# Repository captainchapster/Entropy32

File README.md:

# Entropy32

**Entropy32** (aka *The Universe Bifurcator*) is a dedicated Bitcoin seed phrase generator that uses radioactive decay as its entropy source. It's completely open source and designed to be simple, auditable, and buildable by anyone with readily available components.

## Why radioactive decay?

Pseudo-random number generators are deterministic — given the same seed, they always produce the same output. True randomness for something as consequential as a Bitcoin wallet's seed phrase should come from a physical process nobody can predict or manipulate. Radioactive decay is quantum-mechanically random: the timing of individual decay events is fundamentally unpredictable, making it an ideal entropy source for generating cryptographic secrets.

## How it works

1. A Geiger counter detects decay events from a radioactive source (or background) and outputs a pulse via a 3.5mm audio jack.

2. An LM393 comparator IC then takes the 0-1.5V pulse and compares it to a bias of ~0.5V via a voltage divider such that if V>0.5V we get HIGH else LOW.

3. The timing between events is captured and compared in non-overlapping pairs (each inter-arrival time feeds exactly one comparison, so adjacent output bits never share an input interval). Each resulting bit passes two continuous NIST SP 800-90B health tests (Repetition Count Test and Adaptive Proportion Test) before it's fed through SHA-256 conditioning to whiten the raw entropy and remove any bias — if either test trips, the device halts rather than generating a seed from a degraded source.
4. The conditioned entropy is mapped to words from the standard BIP39 English wordlist.
5. A simple button-driven, state-machine UI walks you through generating and displaying your seed phrase — entirely offline, with no wireless connectivity, no persistent storage of the seed, and no software dependencies beyond the device itself.

## Hardware

- Custom PCB built around an [ATmega328P microcontroller](https://ww1.microchip.com/downloads/en/DeviceDoc/Atmel-7810-Automotive-Microcontrollers-ATmega328P_Datasheet.pdf), designed in [KiCad](https://www.kicad.org/)
- Geiger counter module as the entropy source (currently designed to take the 3.5mm output of the [GQ Electronics GMC-320S](https://www.gqelectronicsllc.com/comersus/store/comersus_viewItem.asp?idProduct=5787))
- [LM393 comparator IC](https://www.ti.com/product/LM393)
- Push-button interface for on-device operation
- Serveral common passives i.e. resistors, capacitors, and LEDs
- 7805 voltage regulator 
- 16MHZ crystal oscillator
- 16x2 LCD display with I2C adaptor
- PJ320E 3.5mm audio jack
- DC barrel jack
- header pins

## Repository contents

| File | Purpose |
|---|---|
| `entropy32.ino` | Main firmware — state machine, entropy capture, and UI logic |
| `sha256.h` / `sha256.cpp` | SHA-256 implementation used to condition raw entropy |
| `bip39_wordlist.h` | BIP39 English wordlist, compiled into firmware |
| `button.h` | Button input handling |
| `english.txt` | Source BIP39 wordlist |
| `generate_wordlist.py` | Script to regenerate `bip39_wordlist.h` from `english.txt` |

## Building it yourself

The Arduino sketch (`entropy32.ino`) and its accompanying `.h`/`.cpp` files must remain in the same top-level folder for the Arduino IDE to compile correctly — it doesn't recurse into subfolders for sketch code. Open `entropy32.ino` in the Arduino IDE, verify your board settings for the ATmega328P, and flash as normal.

## Validation

Entropy quality is being validated against the [NIST SP 800-90B](https://csrc.nist.gov/publications/detail/sp/800-90b/final) methodology for entropy sources used in random bit generation.

## Acknowledgements

- **Cosmographer / BHRIGU** — [bhrigu.io](https://www.bhrigu.io) — identified that the original entropy logic compared each inter-arrival time to the one before it (an overlapping comparison), which correlates adjacent output bits even when the underlying intervals are IID. The firmware now uses non-overlapping interval pairs instead. Thank you for the detailed writeup.

## Disclaimer

This is a hobbyist/educational project. If you use it to generate a real Bitcoin seed phrase, understand the risks: verify the entropy quality yourself, review the code, and never trust a seed-generating device (this one included) with significant funds without independent auditing.

## Licenses

- For firmware/software, see [`MIT LICENSE`](./LICENSE).
- For hardware, see [`CERN-OHL-S v2 LICENSE`](./LICENSE-HARDWARE).

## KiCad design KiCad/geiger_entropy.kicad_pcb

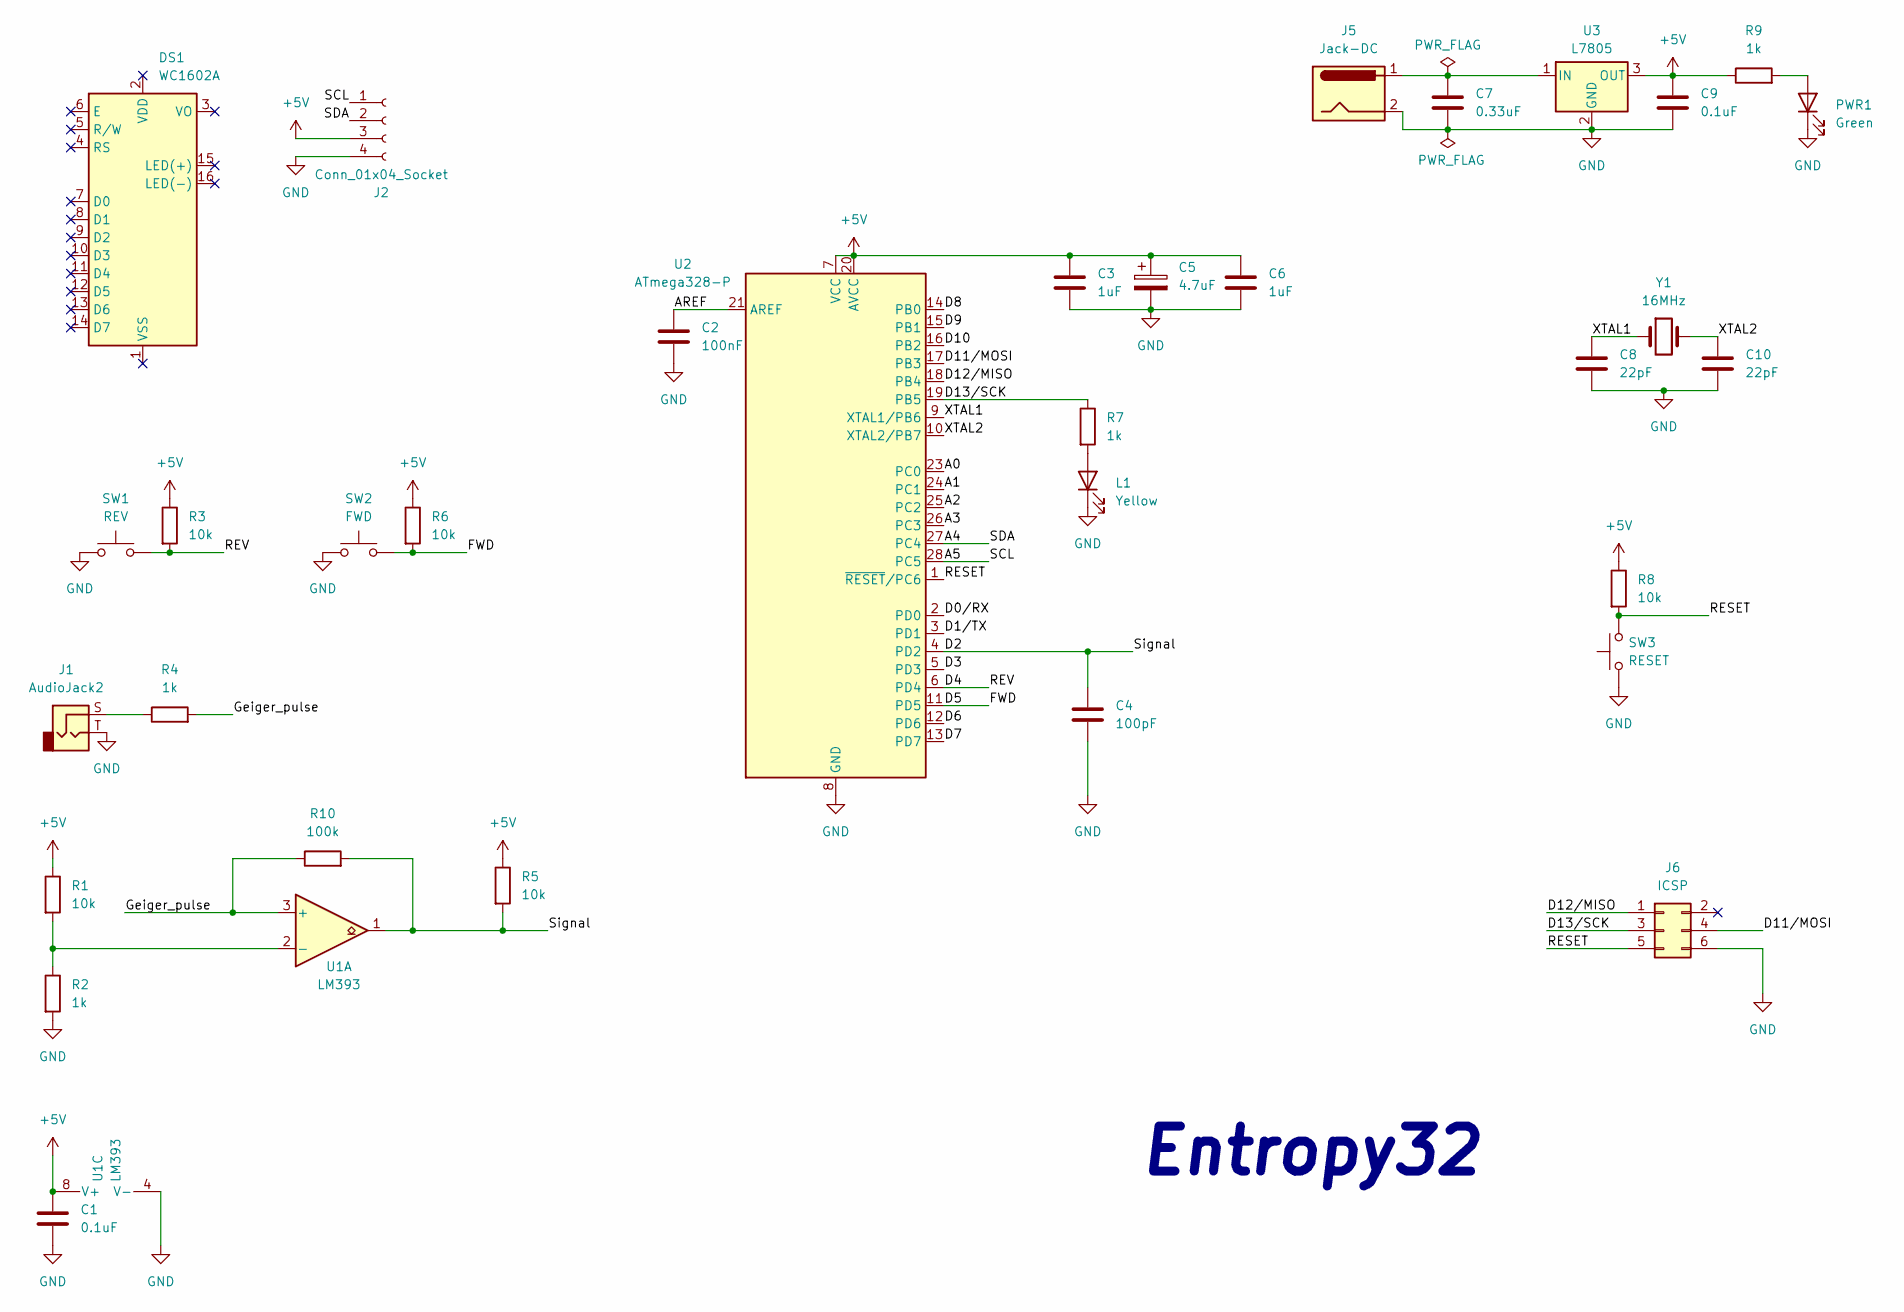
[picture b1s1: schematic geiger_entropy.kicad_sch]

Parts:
C1, C9: 0.1uF; C_Disc_D5.0mm_W2.5mm_P5.00mm
C2: 100nF; C_Disc_D5.0mm_W2.5mm_P5.00mm
C3, C6: 1uF; C_Disc_D5.0mm_W2.5mm_P5.00mm
C4: 100pF; C_Disc_D5.0mm_W2.5mm_P5.00mm
C5: 4.7uF; CP_Radial_D5.0mm_P2.00mm
C7: 0.33uF; C_Disc_D5.0mm_W2.5mm_P5.00mm
C8, C10: 22pF; C_Disc_D5.0mm_W2.5mm_P5.00mm
DS1: WC1602A
J1: AudioJack2; Jack_3.5mm_PJ320E_Horizontal
J2: Conn_01x04_Socket; PinHeader_1x04_P2.54mm_Vertical
J5: Jack-DC; BarrelJack_Horizontal
J6: ICSP; PinHeader_2x03_P2.54mm_Vertical
L1: Yellow; LED_D3.0mm
PWR1: Green; LED_D3.0mm
R1, R3, R5, R6, R8: 10k; R_Axial_DIN0207_L6.3mm_D2.5mm_P10.16mm_Horizontal
R2, R4, R7, R9: 1k; R_Axial_DIN0207_L6.3mm_D2.5mm_P10.16mm_Horizontal
R10: 100k; R_Axial_DIN0207_L6.3mm_D2.5mm_P10.16mm_Horizontal
SW1: REV; SW_PUSH_6mm
SW2: FWD; SW_PUSH_6mm
SW3: RESET; SW_PUSH_6mm
U1: LM393; DIP-8_W7.62mm
U2: ATmega328-P; DIP-28_W7.62mm
U3: L7805; TO-220-3_Vertical
Y1: 16MHz; Crystal_HC49-4H_Vertical

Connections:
+5V: C1.1, C3.1, C5.1, C6.1, C9.1, J2.3, R1.1, R3.1, R5.1, R6.1, R8.1, R9.1, U1.8 (V+), U2.7 (VCC), U2.20 (AVCC), U3.3 (OUT)
/A0: U2.23 (PC0)
/A1: U2.24 (PC1)
/A2: U2.25 (PC2)
/A3: U2.26 (PC3)
/A4: J2.2, U2.27 (PC4)
/A5: J2.1, U2.28 (PC5)
/AREF: C2.1, U2.21 (AREF)
/D0/RX: U2.2 (PD0)
/D1/TX: U2.3 (PD1)
/D2: C4.1, R5.2, R10.2, U1.1, U2.4 (PD2)
/D3: U2.5 (PD3)
/D4: R3.2, SW1.2, U2.6 (PD4)
/D5: R6.2, SW2.2, U2.11 (PD5)
/D6: U2.12 (PD6)
/D7: U2.13 (PD7)
/D8: U2.14 (PB0)
/D9: U2.15 (PB1)
/D10: U2.16 (PB2)
/D11/MOSI: J6.4, U2.17 (PB3)
/D12/MISO: J6.1, U2.18 (PB4)
/D13/SCK: J6.3, R7.1, U2.19 (PB5)
/Geiger_pulse: R4.2, R10.1, U1.3 (+)
/RESET: J6.5, R8.2, SW3.2, U2.1 (~RESET/PC6)
/XTAL1: C8.1, U2.9 (XTAL1/PB6), Y1.1
/XTAL2: C10.1, U2.10 (XTAL2/PB7), Y1.2
GND: C1.2, C2.2, C3.2, C4.2, C5.2, C6.2, C7.2, C8.2, C9.2, C10.2, J1.T, J2.4, J5.2, J6.6, L1.1 (K), PWR1.1 (K), R2.2, SW1.1, SW2.1, SW3.1, U1.4 (V-), U2.8 (GND), U2.22 (GND), U3.2 (GND)
unnamed: J1.S, R4.1
unnamed: L1.2 (A), R7.2
unnamed: PWR1.2 (A), R9.2
unnamed: R1.2, R2.1, U1.2 (-)
unnamed: C7.1, J5.1, U3.1 (IN)

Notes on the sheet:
Entropy32

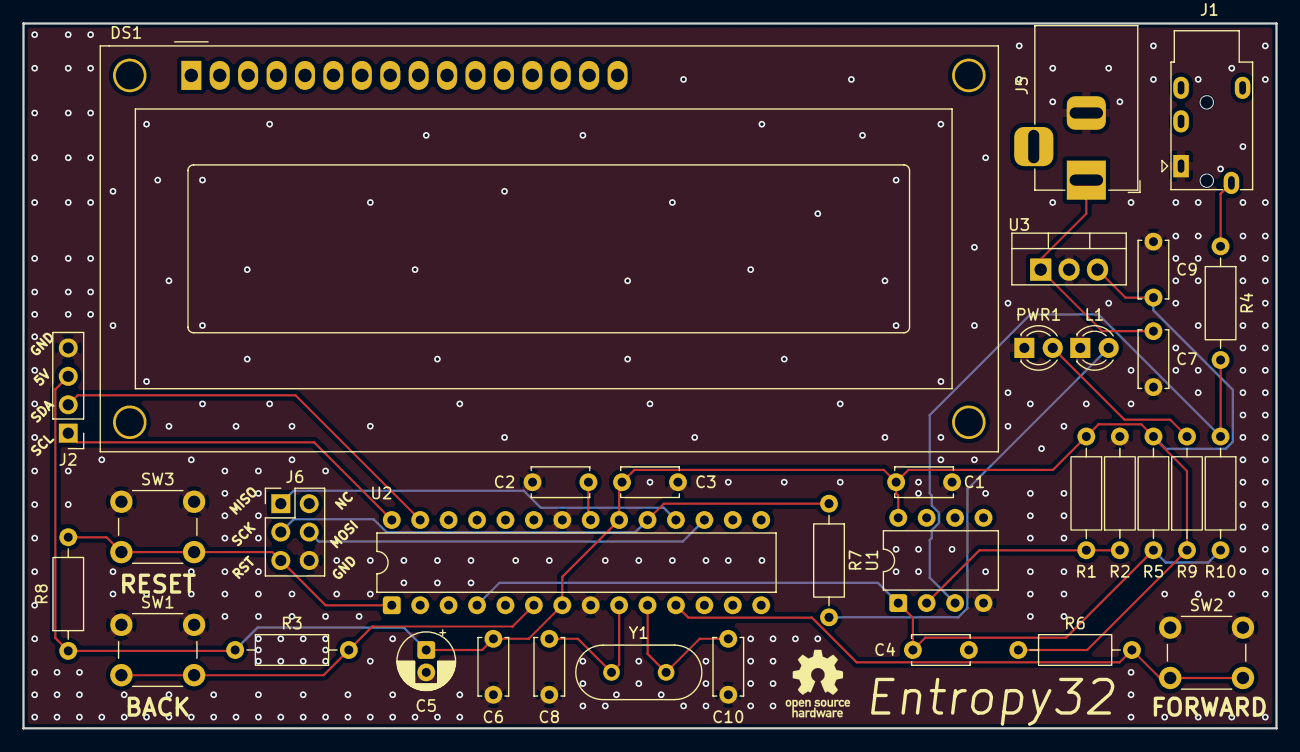
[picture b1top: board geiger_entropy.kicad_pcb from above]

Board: 2 copper layers, 112.0 x 63.0 mm, 34 parts (0 on the bottom side), 20 nets.

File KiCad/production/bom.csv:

Designator,Footprint,Quantity,Value,LCSC Part #
"C1, C9",C_Disc_D5.0mm_W2.5mm_P5.00mm,2,0.1uF,
"C10, C8",C_Disc_D5.0mm_W2.5mm_P5.00mm,2,22pF,
C2,C_Disc_D5.0mm_W2.5mm_P5.00mm,1,100nF,
"C3, C6",C_Disc_D5.0mm_W2.5mm_P5.00mm,2,1uF,
C4,C_Disc_D5.0mm_W2.5mm_P5.00mm,1,100pF,
C5,CP_Radial_D5.0mm_P2.00mm,1,4.7uF,
C7,C_Disc_D5.0mm_W2.5mm_P5.00mm,1,0.33uF,
DS1,WC1602A,1,WC1602A,
J1,Jack_3.5mm_PJ320E_Horizontal,1,AudioJack2,
J2,PinHeader_1x04_P2.54mm_Vertical,1,Conn_01x04_Socket,
J5,BarrelJack_Horizontal,1,Jack-DC,
J6,PinHeader_2x03_P2.54mm_Vertical,1,ICSP,
L1,LED_D3.0mm,1,Yellow,
PWR1,LED_D3.0mm,1,Green,
"R1, R3, R5, R6, R8",R_Axial_DIN0207_L6.3mm_D2.5mm_P10.16mm_Horizontal,5,10k,
R10,R_Axial_DIN0207_L6.3mm_D2.5mm_P10.16mm_Horizontal,1,100k,
"R2, R4, R7, R9",R_Axial_DIN0207_L6.3mm_D2.5mm_P10.16mm_Horizontal,4,1k,
SW1,SW_PUSH_6mm,1,REV,
SW2,SW_PUSH_6mm,1,FWD,
SW3,SW_PUSH_6mm,1,RESET,
U1,DIP-8_W7.62mm,1,LM393,
U2,DIP-28_W7.62mm,1,ATmega328-P,
U3,TO-220-3_Vertical,1,L7805,
Y1,Crystal_HC49-4H_Vertical,1,16MHz,
